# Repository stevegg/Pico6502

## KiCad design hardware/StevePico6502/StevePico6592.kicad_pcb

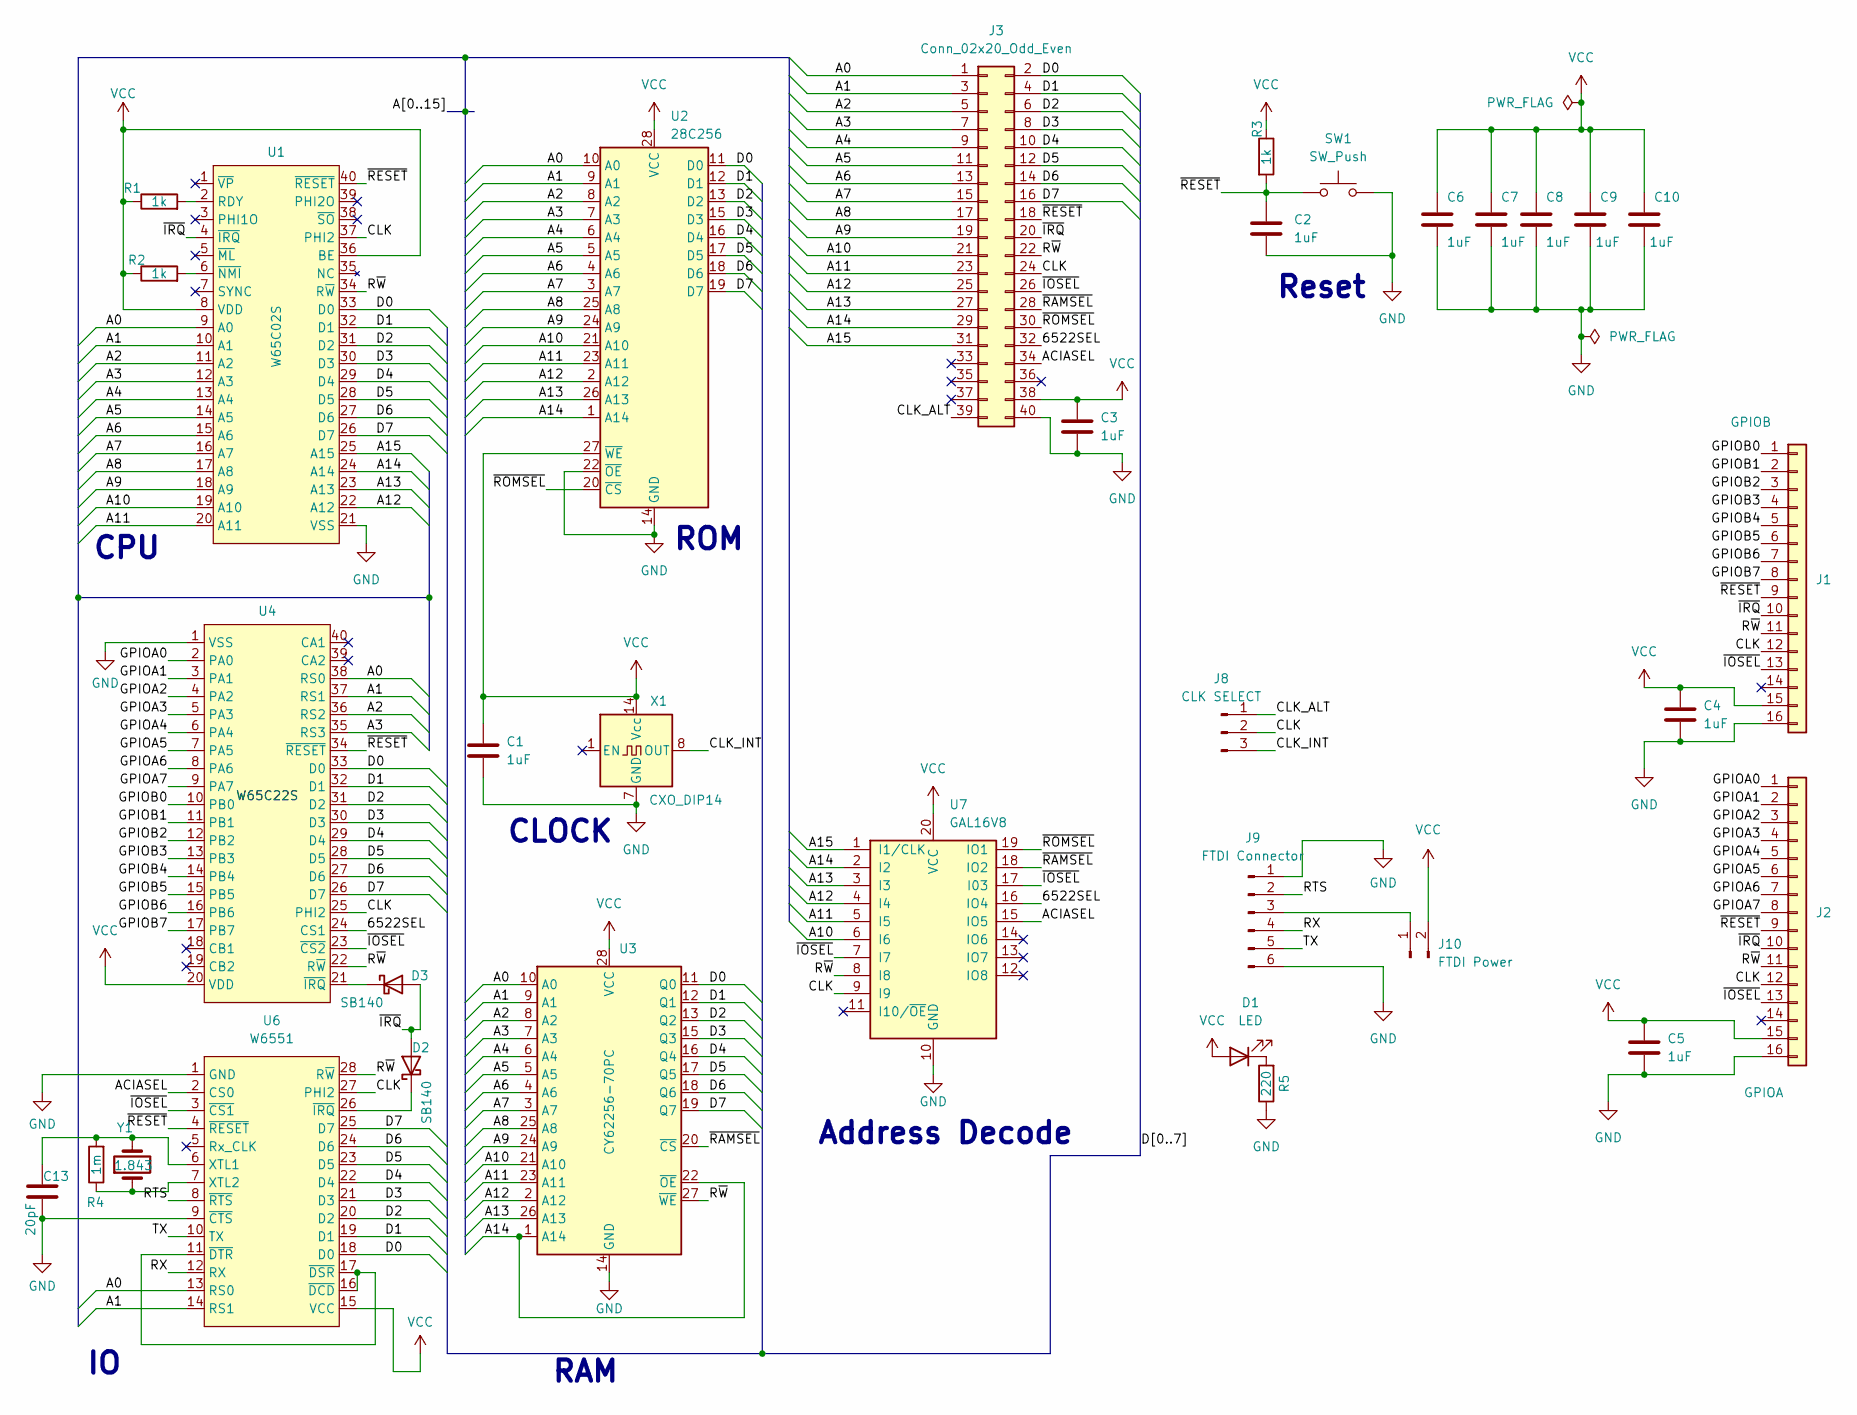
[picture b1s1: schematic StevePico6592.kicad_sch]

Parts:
C1, C2, C3, C4, C5, C6, C7, C8, C9, C10: 1uF; C_Disc_D3.4mm_W2.1mm_P2.50mm
C13: 20pF; C_Disc_D3.4mm_W2.1mm_P2.50mm
D1: LED; LED_D3.0mm_Clear
D2, D3: SB140; D_DO-41_SOD81_P10.16mm_Horizontal
J1: GPIOB; PinHeader_1x16_P2.54mm_Vertical
J2: GPIOA; PinHeader_1x16_P2.54mm_Vertical
J3: Conn_02x20_Odd_Even; PinHeader_2x20_P2.54mm_Vertical
J8: CLK SELECT; PinHeader_1x03_P2.54mm_Vertical
J9: FTDI Connector; PinHeader_1x06_P2.54mm_Vertical
J10: FTDI Power; PinHeader_1x02_P2.54mm_Vertical
R1, R2, R3: 1k; R_Axial_DIN0207_L6.3mm_D2.5mm_P7.62mm_Horizontal
R4: 1m; R_Axial_DIN0207_L6.3mm_D2.5mm_P7.62mm_Horizontal
R5: 220; R_Axial_DIN0207_L6.3mm_D2.5mm_P7.62mm_Horizontal
SW1: SW_Push; SW_PUSH_6mm
U1: W65C02S; DIP-40_W15.24mm_Socket_LongPads
U2: 28C256; DIP-28_W15.24mm
U3: CY62256-70PC; DIP-28_W15.24mm
U4: W65C22S; DIP-40_W15.24mm_Socket_LongPads
U6: W6551; DIP-28_W15.24mm_Socket_LongPads
U7: GAL16V8; DIP-20_W7.62mm_Socket_LongPads
X1: CXO_DIP14; Oscillator_DIP-14
Y1: 1.843; Crystal_HC52-8mm_Vertical

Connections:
/6522SEL: J3.32, U4.24 (CS1), U7.16 (IO4)
/A0: J3.1, U1.9 (A0), U2.10 (A0), U3.10 (A0), U4.38 (RS0), U6.13 (RS0)
/A1: J3.3, U1.10 (A1), U2.9 (A1), U3.9 (A1), U4.37 (RS1), U6.14 (RS1)
/A2: J3.5, U1.11 (A2), U2.8 (A2), U3.8 (A2), U4.36 (RS2)
/A3: J3.7, U1.12 (A3), U2.7 (A3), U3.7 (A3), U4.35 (RS3)
/A4: J3.9, U1.13 (A4), U2.6 (A4), U3.6 (A4)
/A5: J3.11, U1.14 (A5), U2.5 (A5), U3.5 (A5)
/A6: J3.13, U1.15 (A6), U2.4 (A6), U3.4 (A6)
/A7: J3.15, U1.16 (A7), U2.3 (A7), U3.3 (A7)
/A8: J3.17, U1.17 (A8), U2.25 (A8), U3.25 (A8)
/A9: J3.19, U1.18 (A9), U2.24 (A9), U3.24 (A9)
/A10: J3.21, U1.19 (A10), U2.21 (A10), U3.21 (A10), U7.6 (I6)
/A11: J3.23, U1.20 (A11), U2.23 (A11), U3.23 (A11), U7.5 (I5)
/A12: J3.25, U1.22 (A12), U2.2 (A12), U3.2 (A12), U7.4 (I4)
/A13: J3.27, U1.23 (A13), U2.26 (A13), U3.26 (A13), U7.3 (I3)
/A14: J3.29, U1.24 (A14), U2.1 (A14), U3.1 (A14), U3.22 (~OE), U7.2 (I2)
/A15: J3.31, U1.25 (A15), U7.1 (I1/CLK)
/ACIASEL: J3.34, U6.2 (CS0), U7.15 (IO5)
/CLK: J1.12, J2.12, J3.24, J8.2, U1.37 (PHI2), U4.25 (PHI2), U6.27 (PHI2), U7.9 (I9)
/CLK_ALT: J3.39, J8.1
/CLK_INT: J8.3, X1.8 (OUT)
/D0: J3.2, U1.33 (D0), U2.11 (D0), U3.11 (Q0), U4.33 (D0), U6.18 (D0)
/D1: J3.4, U1.32 (D1), U2.12 (D1), U3.12 (Q1), U4.32 (D1), U6.19 (D1)
/D2: J3.6, U1.31 (D2), U2.13 (D2), U3.13 (Q2), U4.31 (D2), U6.20 (D2)
/D3: J3.8, U1.30 (D3), U2.15 (D3), U3.15 (Q3), U4.30 (D3), U6.21 (D3)
/D4: J3.10, U1.29 (D4), U2.16 (D4), U3.16 (Q4), U4.29 (D4), U6.22 (D4)
/D5: J3.12, U1.28 (D5), U2.17 (D5), U3.17 (Q5), U4.28 (D5), U6.23 (D5)
/D6: J3.14, U1.27 (D6), U2.18 (D6), U3.18 (Q6), U4.27 (D6), U6.24 (D6)
/D7: J3.16, U1.26 (D7), U2.19 (D7), U3.19 (Q7), U4.26 (D7), U6.25 (D7)
/GPIOA0: J2.1, U4.2 (PA0)
/GPIOA1: J2.2, U4.3 (PA1)
/GPIOA2: J2.3, U4.4 (PA2)
/GPIOA3: J2.4, U4.5 (PA3)
/GPIOA4: J2.5, U4.6 (PA4)
/GPIOA5: J2.6, U4.7 (PA5)
/GPIOA6: J2.7, U4.8 (PA6)
/GPIOA7: J2.8, U4.9 (PA7)
/GPIOB0: J1.1, U4.10 (PB0)
/GPIOB1: J1.2, U4.11 (PB1)
/GPIOB2: J1.3, U4.12 (PB2)
/GPIOB3: J1.4, U4.13 (PB3)
/GPIOB4: J1.5, U4.14 (PB4)
/GPIOB5: J1.6, U4.15 (PB5)
/GPIOB6: J1.7, U4.16 (PB6)
/GPIOB7: J1.8, U4.17 (PB7)
/RTS: J9.2, U6.8 (~RTS)
/RX: J9.4, U6.12 (RX)
/R~W: J1.11, J2.11, J3.22, U1.34 (R~W), U3.27 (~WE), U4.22 (R~W), U6.28 (R~W), U7.8 (I8)
/TX: J9.5, U6.10 (TX)
/~IOSEL: J1.13, J2.13, J3.26, U4.23 (~CS2), U6.3 (~CS1), U7.7 (I7), U7.17 (I03)
/~IRQ: D2.2 (A), D3.2 (A), J1.10, J2.10, J3.20, U1.4 (~IRQ)
/~RAMSEL: J3.28, U3.20 (~CS), U7.18 (IO2)
/~RESET: C2.1, J1.9, J2.9, J3.18, R3.2, SW1.1, U1.40 (~RESET), U4.34 (~RESET), U6.4 (~RESET)
/~ROMSEL: J3.30, U2.20 (~CS), U7.19 (IO1)
GND: C1.2, C2.2, C3.2, C4.2, C5.2, C6.2, C7.2, C8.2, C9.2, C10.2, C13.2, J1.16, J2.16, J3.40, J9.1, J9.6, R5.1, SW1.2, U1.21 (VSS), U2.14 (GND), U2.22 (~OE), U3.14 (GND), U4.1 (VSS), U6.1 (GND), U6.9 (~CTS), U7.10 (GND), X1.7 (GND); also elsewhere on the board
unnamed: D1.1 (K), R5.2
unnamed: D2.1 (K), U6.26 (~IRQ)
unnamed: D3.1 (K), U4.21 (~IRQ)
unnamed: J9.3, J10.1
unnamed: R1.2, U1.2 (RDY)
unnamed: R2.2, U1.6 (~NMI)
unnamed: C13.1, R4.2, U6.6 (XTL1), Y1.2
unnamed: R4.1, U6.7 (XTL2), Y1.1
unnamed: U6.11 (~DTR), U6.16 (~DCD), U6.17 (~DSR)
VCC: C1.1, C3.1, C4.1, C5.1, C6.1, C7.1, C8.1, C9.1, C10.1, D1.2 (A), J1.15, J2.15, J3.38, J10.2, R1.1, R2.1, R3.1, U1.8 (VDD), U1.36 (BE), U2.27 (~WE), U2.28 (VCC), U3.28 (VCC), U4.20 (VDD), U6.15 (VCC), U7.20 (VCC), X1.14 (Vcc); also elsewhere on the board

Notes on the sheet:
Reset
Address Decode
RAM
ROM
CPU
CLOCK

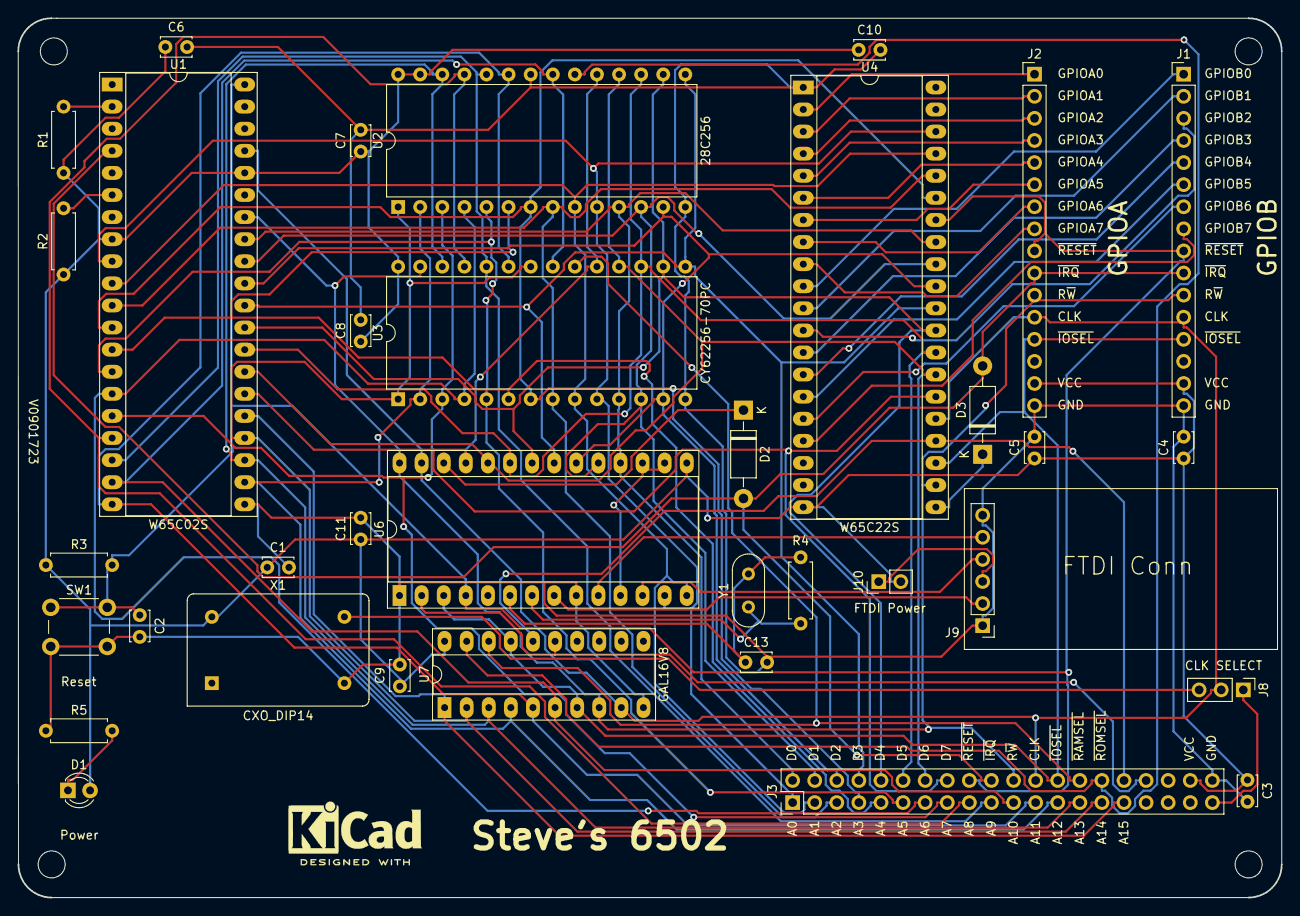
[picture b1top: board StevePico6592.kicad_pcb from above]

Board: 2 copper layers, 145.3 x 101.1 mm, 35 parts (0 on the bottom side), 65 nets.

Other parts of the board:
C11: 1uF; C_Disc_D3.4mm_W2.1mm_P2.50mm

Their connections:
GND: C11.2; also elsewhere on the board
VCC: C11.1; also elsewhere on the board

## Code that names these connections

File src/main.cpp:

#include <Arduino.h>
#include "incbin.h"
#include "server.h"

// INCBIN(romSource, "./6502 src/lcdHelloWorld.bin");
INCBIN(romSource, "./6502 src/test.bin");

#define PICO6502_RESETVEC 0xfffc
#define PICO6502_RAM_BASE 0x0000
#define PICO6502_ROM_BASE 0x8000
#define PICO6502_IO_BASE 0x6000
#define DELAY_74HC595 1
#define STEP_DELAY 50
#define ROM_SIZE 32768
// #define USE_GPIO_FUNCS 1

uint32_t stepDelay = 50;

//                         A0, A1, A2, A3, A4, A5, A6, A7
const int addressPins[] = {28, 27, 26, 22, 21, 20, 19, 18, 17, 16, 15, 14, 13, 12, 11, 10};

// 74HC595 Shift Register Pins
const int dataPin = 2;
const int latchPin = 3;
const int serClkPin = 4;

// 6502 Control lines
const int clkPin = 0;
const int rwPin = 1;

// Address decoding pins
const int ramSelPin = 5;
const int ioSelPin = 6;
const int romSelPin = 7;

// Other
const int stepPin = 9;

byte *rom = NULL;

void strobeLatchPin(int value)
{
  digitalWrite(serClkPin, LOW);
  sleep_us(DELAY_74HC595);
  digitalWrite(latchPin, value);
  sleep_us(DELAY_74HC595);
  digitalWrite(serClkPin, HIGH);
  sleep_us(DELAY_74HC595);
}

void writeDataBit(int value)
{
  digitalWrite(serClkPin, LOW);
  sleep_us(DELAY_74HC595);
  digitalWrite(dataPin, value);
  sleep_us(DELAY_74HC595);
  digitalWrite(serClkPin, HIGH);
  sleep_us(DELAY_74HC595);
}

byte writeDataBus(byte value)
{
  strobeLatchPin(LOW);
  for (int i = 7; i >= 0; i--)
  {
    int bit = (value & (1 << i)) ? 1 : 0;
    writeDataBit(bit);
  }
  strobeLatchPin(HIGH);
  return value;
}

word readAddressBus()
{
  word value = 0;
  for (int i = 0; i < 16; i++)
  {
    value |= (digitalRead(addressPins[i]) ? 1 : 0) << i;
  }
  return value;
}

bool singleStep = false;
char addrType[10];
char buffer[200];

void step()
{
  byte data = 0x00;

  // Turn on LED on to indicate we're processing
  digitalWrite(LED_BUILTIN, HIGH);
  // CLK goes LOW
  digitalWrite(clkPin, LOW);

  // Read signal pins
  bool reading = digitalRead(rwPin);
  word address = readAddressBus();

  bool ramSel = (address < PICO6502_IO_BASE);
  bool ioSel = (address >= PICO6502_IO_BASE && address < PICO6502_ROM_BASE);
  bool romSel = (address >= PICO6502_ROM_BASE);

  // Since these outputs are active LOW invert the value of the booleans
  digitalWrite(ramSelPin, !ramSel);
  digitalWrite(ioSelPin, !ioSel);
  digitalWrite(romSelPin, !romSel);

  data = (reading && romSel) ? writeDataBus(rom[address - PICO6502_ROM_BASE]) : 0x00;

  if (singleStep)
  {
    // Output current status to Serial port
    sprintf(buffer, "BUS Addr: %s : %4.4X - Data: %2.2X - DIR: %c",
            (ramSel) ? "RAM" : (ioSel) ? "IO "
                           : (romSel)  ? "ROM"
                                       : "???",
            address, (reading && romSel) ? data : 0x00, reading ? 'R' : 'W');
    Serial.println(buffer);
  }

  // Delay
  // sleep_ms((singleStep) ? 0 : STEP_DELAY);

  // Turn off LED
  digitalWrite(LED_BUILTIN, LOW);
  // Set CLK HIGH
  digitalWrite(clkPin, HIGH);
}

void setup()
{

  //
#ifdef USE_GPIO_FUNCS
  gpio_set_dir(LED_BUILTIN, GPIO_OUT);

  // IOSelect
  gpio_set_dir(ioSelPin, GPIO_OUT);
  gpio_put(ioSelPin, HIGH);

  // RAMSelect set to HIGH initially
  gpio_set_dir(ramSelPin, GPIO_OUT);
  gpio_put(ramSelPin, HIGH);

  // ROMSelect set to HIGH
  gpio_set_dir(romSelPin, GPIO_OUT);
  gpio_put(romSelPin, HIGH);

  // Setup pins for outputting to the databus via the 74HC595
  gpio_set_dir(dataPin, GPIO_OUT);
  gpio_set_dir(latchPin, GPIO_OUT);
  gpio_set_dir(serClkPin, GPIO_OUT);

  gpio_put(latchPin, HIGH);
  gpio_put(serClkPin, HIGH);
  gpio_put(dataPin, LOW);

  // Step button setup as a PULLUP Input
  gpio_set_dir(stepPin, GPIO_IN);
  gpio_pull_up(stepPin);

  for (int i = 0; i < 16; i++)
  {
    // Address pins are input
    gpio_set_dir(addressPins[i], GPIO_IN);
  }
  // CLK is an output
  gpio_set_dir(clkPin, GPIO_OUT);
  gpio_put(clkPin, HIGH);

  // RW pin is an input
  gpio_set_dir(rwPin, GPIO_IN);

#else
  // Builtin LED
  pinMode(LED_BUILTIN, OUTPUT);

  // IOSelect set to HIGH initially
  pinMode(ioSelPin, OUTPUT);
  digitalWrite(ioSelPin, HIGH);

  // RAMSelect set to HIGH initially
  pinMode(ramSelPin, OUTPUT);
  digitalWrite(ramSelPin, HIGH);

  // ROMSelect set to HIGH
  pinMode(romSelPin, OUTPUT);
  digitalWrite(romSelPin, HIGH);

  // Setup pins for outputting to the databus via the 74HC595
  pinMode(dataPin, OUTPUT);
  pinMode(latchPin, OUTPUT);
  pinMode(serClkPin, OUTPUT);

  digitalWrite(latchPin, HIGH);
  digitalWrite(serClkPin, HIGH);
  digitalWrite(dataPin, LOW);

  // Step button
  pinMode(stepPin, INPUT_PULLDOWN);

  for (int i = 0; i < 16; i++)
  {
    // Address pins are input
    pinMode(addressPins[i], INPUT);
  }
  // CLK is an output
  pinMode(clkPin, INPUT);
  digitalWrite(clkPin, HIGH);

  // RW pin is an input
  pinMode(rwPin, INPUT);

  attachInterrupt(digitalPinToInterrupt(clkPin), step, FALLING);

#endif

  Serial.begin(9600);
  sleep_ms(5000);

  // Setup ROM
  rom = (byte *)malloc(ROM_SIZE);
  memset(rom, 0, ROM_SIZE);
  memcpy(rom, gromSourceData, gromSourceSize);
  word resetVectorROMAddress = PICO6502_RESETVEC - PICO6502_ROM_BASE;
  char localBuff[80];
  sprintf(localBuff, "Reset Vector address in ROM is %4.4X", resetVectorROMAddress);
  Serial.println(localBuff);
  rom[resetVectorROMAddress] = lowByte(PICO6502_ROM_BASE);
  rom[resetVectorROMAddress + 1] = highByte(PICO6502_ROM_BASE);
  sprintf(localBuff, "Copied %2.2X bytes from romSource to RAM");
  Serial.println(localBuff);

  Serial.println("Pico6502 Starting...");
}

unsigned char button_checker;

void loop()
{

  if (singleStep)
  {
    button_checker <<= 1;
    button_checker += digitalRead(stepPin);

    if (button_checker == 0x80)
    {
      step();
    }
  }
  else
  {
    step();
  }
  sleep_ms(stepDelay);
}

// // Network Code on second core
// const char *ssid = "GIoT";
// const char *password = "IC7610B4by!";

// void setSpeed(arduino::String value) {
//   Serial.print("Route matched and callback called with value:");
//   Serial.println(value);
//   stepDelay = value.toInt();
// }

// void setup1() {
//   // Start Serial Monitor
//   Serial.begin(9600);

//   // Initialize the LED as an output
//   pinMode(LED_BUILTIN, OUTPUT);

//   // Set LED off
//   digitalWrite(LED_BUILTIN, LOW);

//   setupServer(ssid, password);
//   registerRoute("GET /speed/", setSpeed);

// }

// void loop1() {

//   processServerClient();

// }

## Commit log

2023-08-22 Working with 74hc595 for data bus
2023-08-24 Checkpoint - Working but not super fast
2023-08-25 Sent to JLCPCB for fab. Marker V082323
2023-08-28 fixed bug with dual RAMSEL and no ROMSEL
2023-08-28 Added Pi Pico KiCad library as a submodule
2023-09-03 V090323 - Removed Pico
2023-09-04 new directio
2023-09-04 6502 Rev 2
2023-09-05 V090423
2023-09-15 Working on ACIA
2023-09-18 V091723 before fab
2023-09-26 'V091723'
2023-10-08 chore: updated GAL
